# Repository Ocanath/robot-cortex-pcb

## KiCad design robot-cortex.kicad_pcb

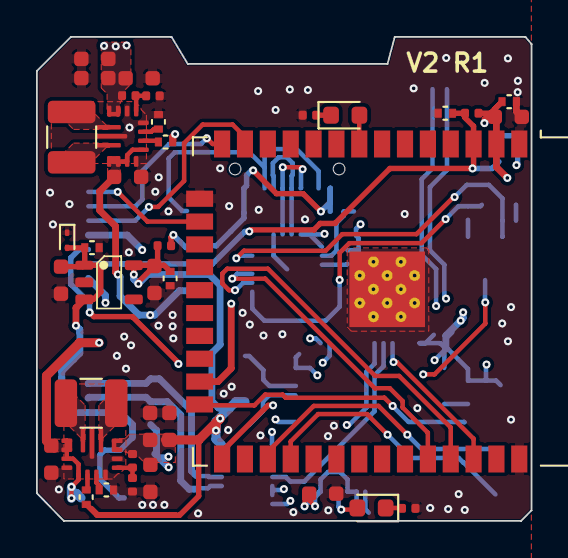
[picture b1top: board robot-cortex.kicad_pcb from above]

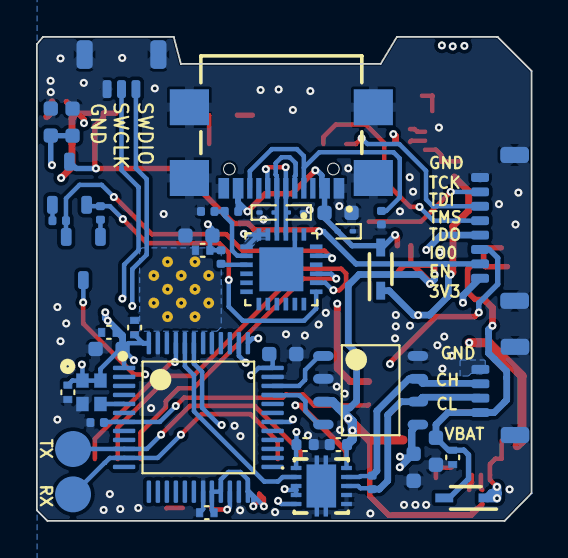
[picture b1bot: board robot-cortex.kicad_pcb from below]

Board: 4 copper layers, 27.5 x 26.9 mm, 79 parts (42 on the bottom side), 51 nets.

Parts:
C1, C3, C6, C8, C10, C12, C14, C15, C19, C21, C23, C26, C35, C36: 100nF; C_0402_1005Metric
C2, C5, C7, C9, C11, C13, C24, C27, C29, C30, C32, C33, C34: C2998534; C_0603_1608Metric
C4, C16, C17, C18, C20: 4.7uF; C_0603_1608Metric
C22, C25: C386081; C_0603_1608Metric
D1, D2, D3, D8: ESD9B3.3ST5G; D_SOD-923
D4, D7: C84264; LED_0603_1608Metric
D5, D6: NSR0530HT1G; SOD2512X110N
IC1: THVD2410VDRCR
J1: USB4110GFA; GCT_USB4110GFA
L1, L2: 1277AS-H-1R0M=P2; L_1210_3225Metric
M1, M2: THRU_HOLE_PAD; TEARDROP
Q1, Q2: SS8050-G; SOT-23-3
R1: 5.1k; R_0402_1005Metric
R2: 4.7k; R_0402_1005Metric
R3, R17: 470; R_0402_1005Metric
R4, R5, R6: 10k; R_0402_1005Metric
R7: 22k; R_0402_1005Metric
R8: 47.5k; R_0402_1005Metric
R9: 1k; R_0402_1005Metric
R10: 470k; R_0402_1005Metric
R11: 150k; R_0402_1005Metric
R12, R15: 100k; C_0402_1005Metric
R13: 680k; R_0402_1005Metric
R14: 130k; R_0402_1005Metric
R16: 0; R_0402_1005Metric
R19: 120; R_0402_1005Metric
U1: C2901617; ECS-1633-480-BN-TR
U2: STM32G431CBT6; LQFP48-STM32
U3: TLE9250XSJXUMA1; SOIC8-TLE5009
U4: DF52-3S-0.8H(21)
U5: DF52-4S-0.8H(21)
U6: SPX3819M5-L-5-0; SOT-23-5
U7: DF52-8S-0.8H(21)
U8: ESP32-WROOM-32E-H4; ESP32-WROOM-32
U9: CP2102N-A02-GQFN24R; QFN50P400X400X80-25N
U10, U11: TPS63070; VQFN-TPS63070

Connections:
+3V3: C1.2, C2.1, C3.1, C5.1, C6.1, C7.1, C8.1, C9.1, C10.1, C16.1, C17.1, C18.1, C19.1, C20.1, C21.1, C27.1, C29.1, C30.1, IC1.1 (VIO), R4.2, R9.2, R10.1, R12.1, U1.1 (Enable/Disable), U1.4 (VDD), U2.1 (VBAT), U2.20 (VREF+), U2.21 (VDDA), U2.24 (VDD), U2.36 (VDD), U2.48 (VDD), U3.5 (VIO), U7.1, U8.2 (3V3), U9.5 (VIO), U9.6 (VDD), U9.7 (VREGIN), U10.7,8 (VOUT)
/+5V0: C13.1, C14.1, C24.1, C32.1, C33.1, C36.2, IC1.10 (VCC), R13.1, R15.1, R16.2, U3.3 (Vcc), U6.5 (VOUT), U11.7,8 (VOUT)
/BOOT: U2.45 (PB8), U8.36 (IO22)
/C+: IC1.9 (B), R19.2, U3.7 (CANH), U5.3
/C-: IC1.8 (A), R19.1, U3.6 (CANL), U5.2
/D+: D2.2 (A2), J1.A6 (DP1), J1.B6 (DP2), U9.3 (D+)
/D-: D1.2 (A2), J1.A7 (DN1), J1.B7 (DN2), U9.4 (D-)
/ESP32/CP210x_RX: U8.35 (TXD0), U9.20 (RXD)
/ESP32/CP210x_TX: U8.34 (RXD0), U9.21 (TXD)
/ESP32/CP210x_VBUS: R7.1, R8.2, U9.8 (VBUS)
/ESP32/DTR: Q2.2 (E), R6.1, U9.23 (~DTR)
/ESP32/EN: C15.1, Q1.3 (C), R4.1, U7.2, U8.3 (EN)
/ESP32/IO0: Q2.3 (C), U7.3, U8.25 (IO0)
/ESP32/RTS: Q1.2 (E), R5.1, U9.19 (~RTS)
/ESP32/TCK: U7.7, U8.16 (IO13/MTCK)
/ESP32/TDI: U7.6, U8.14 (IO12/MTDI)
/ESP32/TDO: U7.4, U8.23 (IO15/MTDO)
/ESP32/TMS: U7.5, U8.13 (IO14/MTMS)
/FDCAN1_RX: U2.33 (PA11), U3.4 (RxD)
/FDCAN1_TX: U2.34 (PA12), U3.1 (TxD)
/LED: D4.2 (A), U2.22 (PB10)
/NRST: R2.1, U2.7 (PG10-NRST), U8.24 (IO2)
/PSU_TPS63070RNMR1/FB: R13.2, R14.1, U11.5 (FB)
/PSU_TPS63070RNMR/FB: R10.2, R11.1, U10.5 (FB)
/SWCLK: U2.38 (PA14), U4.2
/SWDIO: U2.37 (PA13), U4.1
/UART1_DE: IC1.3 (DE), IC1.4 (~RE), U2.30 (PA8)
/UART1_RX: IC1.2 (R), U2.44 (PB7)
/UART1_TX: IC1.5 (D), U2.43 (PB6)
/UART2_RX: M2.1, U2.11 (PA3), U8.28 (IO17)
/UART2_TX: M1.1, U2.10 (PA2), U8.27 (IO16)
/VBAT: C11.1, C12.1, C34.1, C35.1, D5.2 (A), D8.2 (A2), U5.1, U6.1 (VIN), U6.3 (EN)
/VDD_MIXED: C22.1, C25.1, D5.1 (K), D6.1 (K), U10.1 (PS/SYNC), U10.12,13 (VIN), U10.14 (EN), U11.1 (PS/SYNC), U11.12,13 (VIN), U11.14 (EN)
/VUSB: C4.1, D3.2 (A2), D6.2 (A), J1.A4/B9 (VBUS), J1.B4/A9 (VBUS__1), R7.2, R16.1
GND: C1.1, C2.2, C3.2, C4.2, C5.2, C6.2, C7.2, C8.2, C9.2, C10.2, C11.2, C12.2, C13.2, C14.2, C15.2, C16.2, C17.2, C18.2, C19.2, C20.2, C21.2, C22.2, C23.2, C24.2, C25.2, C26.2, C27.2, C29.2, C30.2, C32.2, C33.2, C34.2, C35.2, C36.1, D1.1 (A1), D2.1 (A1), D3.1 (A1), D8.1 (A1), IC1.6 (GND), IC1.7 (SLR), IC1.11 (EP_1), IC1.12 (EP_2), IC1.13 (EP_3), IC1.14 (EP_4), IC1.15 (EP_5), J1.A1/B12 (GND), J1.B1/A12 (GND__1), J1.S1 (GND__2), J1.S2 (GND__3), J1.S3 (GND__4), J1.S4 (GND__5), R1.1, R2.2, R3.2, R8.1, R11.2, R14.2, R17.2, U1.2 (GND/Case), U2.19 (VSSA), U2.23 (VSS), U2.35 (VSS), U2.47 (VSS), U3.2 (GND), U3.8 (RM), U4.3, U4.4 (MNT), U4.5 (MNT), U5.4, U5.5 (MNT), U5.6 (MNT), U6.2 (GND), U7.8, U7.9 (MNT), U7.10 (MNT), U8.1 (GND), U8.15 (GND), U8.38 (GND), U8.39 (P_GND), U9.2 (GND), U9.25 (GND__1), U10.4 (GND), U10.6 (FB2), U10.10 (PGND), U10.15 (VSEL), U11.4 (GND), U11.6 (FB2), U11.10 (PGND), U11.15 (VSEL)
unnamed: D4.1 (K), R3.1
unnamed: D7.2 (A), U8.8 (IO32)
unnamed: D7.1 (K), R17.1
unnamed: J1.A5 (CC1), J1.B5 (CC2), R1.2
unnamed: Q1.1 (B), R6.2
unnamed: Q2.1 (B), R5.2
unnamed: U1.3 (OUTPUT), U2.5 (PF0-OSC_IN)
unnamed: R9.1, U9.9 (~RST)
unnamed: L2.1, U10.11 (L1)
unnamed: L2.2, U10.9 (L2)
unnamed: R12.2, U10.2 (PG)
unnamed: C26.1, U10.3 (VAUX)
unnamed: L1.1, U11.11 (L1)
unnamed: L1.2, U11.9 (L2)
unnamed: R15.2, U11.2 (PG)
unnamed: C23.1, U11.3 (VAUX)

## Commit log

2019-06-05 init commit, some good progress on layout and uC schematic. lots of features still needed
2019-06-05 added nrf to schematic
2019-06-10 worked on design of power delivery circuitry. not sure how to do connector layout
2019-06-10 added charging and cp2102 to sch
2019-06-10 added footprints to pcb for usb-com and charging
2019-06-17 layout progress, ish. haven't placed IMU yet. Might just straight up migrate to the 64 pin lqfp format for this board...
2019-06-24 notes and layout progress
2019-06-25 removed power management, will now live on a separate set of pcbs
2019-06-27 major layout progress
2019-06-27 first pass routing complete. need to review features and add NRF antenna, then i'll redo the whole thing again with the 64pin QFN package
2019-06-30 functional and dissatisfying robot master layout. I will try and improve on this design with the 64pin qfn version
2019-06-30 marginally improved layout. more streamlined
2019-06-30 moved in-pad thru hole
2019-06-30 added logo
2019-07-01 layout progess, updated uC in schematic
2019-07-01 layout basically done, changed pinouts. need to review features one more time
2019-07-01 upgraded to stat version of the charging chip. added schematic annotations. tweaked locations of the gpio pins.
2019-07-01 route done. considering making it smaller, but i may hold off in the interest of rf isolation and time...
2019-07-01 poly poured. still unsure whether i will condense
2019-07-02 moved pull up resistor away from pads
2019-07-02 condensed layout somewhat
2019-07-02 cortex rev complete. ready to order
2019-07-06 gerber generated, board ordered
2020-09-03 progress on new version to merge
2020-09-08 notes, added transciever, no significant layout changes
2020-09-09 added load disconnect when usb is plugged in. need to figure out how to switch power to usb...
2020-09-10 power management stage complete
2020-09-10 updated todo
2020-09-10 added usb 3.0 A receptacle to lib.
2020-09-10 layout changes and new usb connector. color updates to net. fixed schematic design mistake (critical)
2020-09-11 oruting projgnress im druuunk so i need for not break everythgins
2020-09-11 drunk jesse updated sch and pcb lib and added pmosese for the power managment
2020-09-15 added flip flop for power switch toggle management. need rc lowpass for debouncing. power management layout needs to be modified to accommodate the new circuitry
2020-09-15 added switch
2020-09-16 added a pullup resistor. idk if this will work. should proably add jumpers to bypass my experimental circuitry
2020-09-16 smoe routing
2020-09-20 design finalized
2020-09-21 almost there
2020-09-22 silk cleanup and attempt at proj variants...
2020-09-22 variant success
2020-09-23 added silk marking for usb. needs bom management
2020-09-27 placed assembly jlc. enormous amoutn of money in this order. feeling nervous
2020-09-27 order submitted and paid
2021-03-15 init commit v2, added schdoc and uc oscillator
2021-03-18 cc1190 and cc1101 schlib
2021-03-23 swapped op amp for schmitt trigger
2021-03-25 added new generic rlc component lib, which i'll probably start transferring to others as a gen purpose intlib or similar. partial progress on the radio layout
2021-05-17 sch form is mostl done. needs oscillator, validation, component values, antenna, SPI+UART mapping to uC
2021-05-24 many updates, including compoment values for CC chips, addition of mpu co-processor
2021-07-08 i think design ready to route
2021-07-08 added power distrib with parallel pmos. because why not.
2021-08-03 routing of radiogit status clean and fairly consistent with example layout
2021-08-04 major routing progress and modification of nrf52 spi pins
2021-08-04 major routing progress
2021-08-04 prog headers
2021-08-04 shifted around pads for hp distrib board
2021-08-04 connector and silk updates
2021-08-04 major layout change for rf no-interfere
2021-08-14 poly update and fencing for rf circuits
2023-07-05 init commit
2024-03-06 added 3dmodels and updated esp32 footprint
2024-03-06 updated value field
2024-03-08 added new esp32 footprint
2024-04-14 added many components
2024-04-14 checked and fixed npn issue, added mpn
2024-04-14 added tvs diodes, schematic review. Probably gonna axe the external uart for this one
2024-04-14 moved esp32 to heirarchichalca
2024-04-14 commit b4 transition to non-coprocessor. most of sch is done which is good
2024-04-14 heirarchichal sheet label error fix
2024-07-31 sch done sans one additional change, of figuring out how to safely connect VUSB to +5V0 on the CAN transciever
2024-07-31 nearly ready to route, need to decide on 5V issue for CAN still
2024-08-01 updated power supply method
2024-08-01 3d models
2024-08-01 cannot route have to sleep but i will be back
2024-08-03 nothing too crazy
2024-08-03 exposed boot and IO0 on jtag connector for esp32
2024-08-03 group layouts nearly done
2024-08-04 ground planes, more routing
2024-08-04 placement mostly done and routing in progress
2024-08-04 lots of routing
2024-08-04 little more routing
2024-08-05 routed, drc not pass
2024-08-05 drc pass
2024-08-05 gnd on esp32
2024-08-05 gnd review
2024-08-05 some shuffling
2024-08-05 labeleled
2024-08-07 mpn correction
2024-08-21 changed for v2
2024-08-21 forgto to save sch
2024-08-21 changes that are tested+working
2024-10-09 rs485
2024-10-11 routed but want to reroute differential pairs
2024-10-11 rerouted
2024-10-11 skew 3mil
2024-10-11 sub 1mm skew on each
2024-10-11 more routing tweaks
2024-10-12 3dmodel
2024-10-13 something changed in the pcb, slight coord shifts
2024-10-15 blah
2025-03-07 rev marker and ordered
2025-03-07 fab plugin jisson
